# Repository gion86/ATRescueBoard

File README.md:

# ATRescueBoard
### Full credit for the original version to Jeff Keyzer [http://mightyohm.com](http://mightyohm.com)

Atmel "rescue" board for ATMega and ATTiny X4/X5: to recover fuses setting with High Voltage Programming. 

The PCB is a simplified Arduino shield, with sockets for ATMega and ATTiny; as 12V source the Vin Arduino 
pin has to be used, so the **Arduino must be powered externally with a 12V power supply!**

The micro code is uploaded to the ATmega328P on the Arduino, and comunicate with the user via the serial
interface. Three different mode can be selected:
* ATMEGA: mode for ATmega 128/168/328;
* TINY2313: not supported in this hardware version, look for original version at [https://mightyohm.com/blog/products/hv-rescue-shield-2-x/](https://mightyohm.com/blog/products/hv-rescue-shield-2-x/);
* HVSP: mode for ATtiny X4/X5;

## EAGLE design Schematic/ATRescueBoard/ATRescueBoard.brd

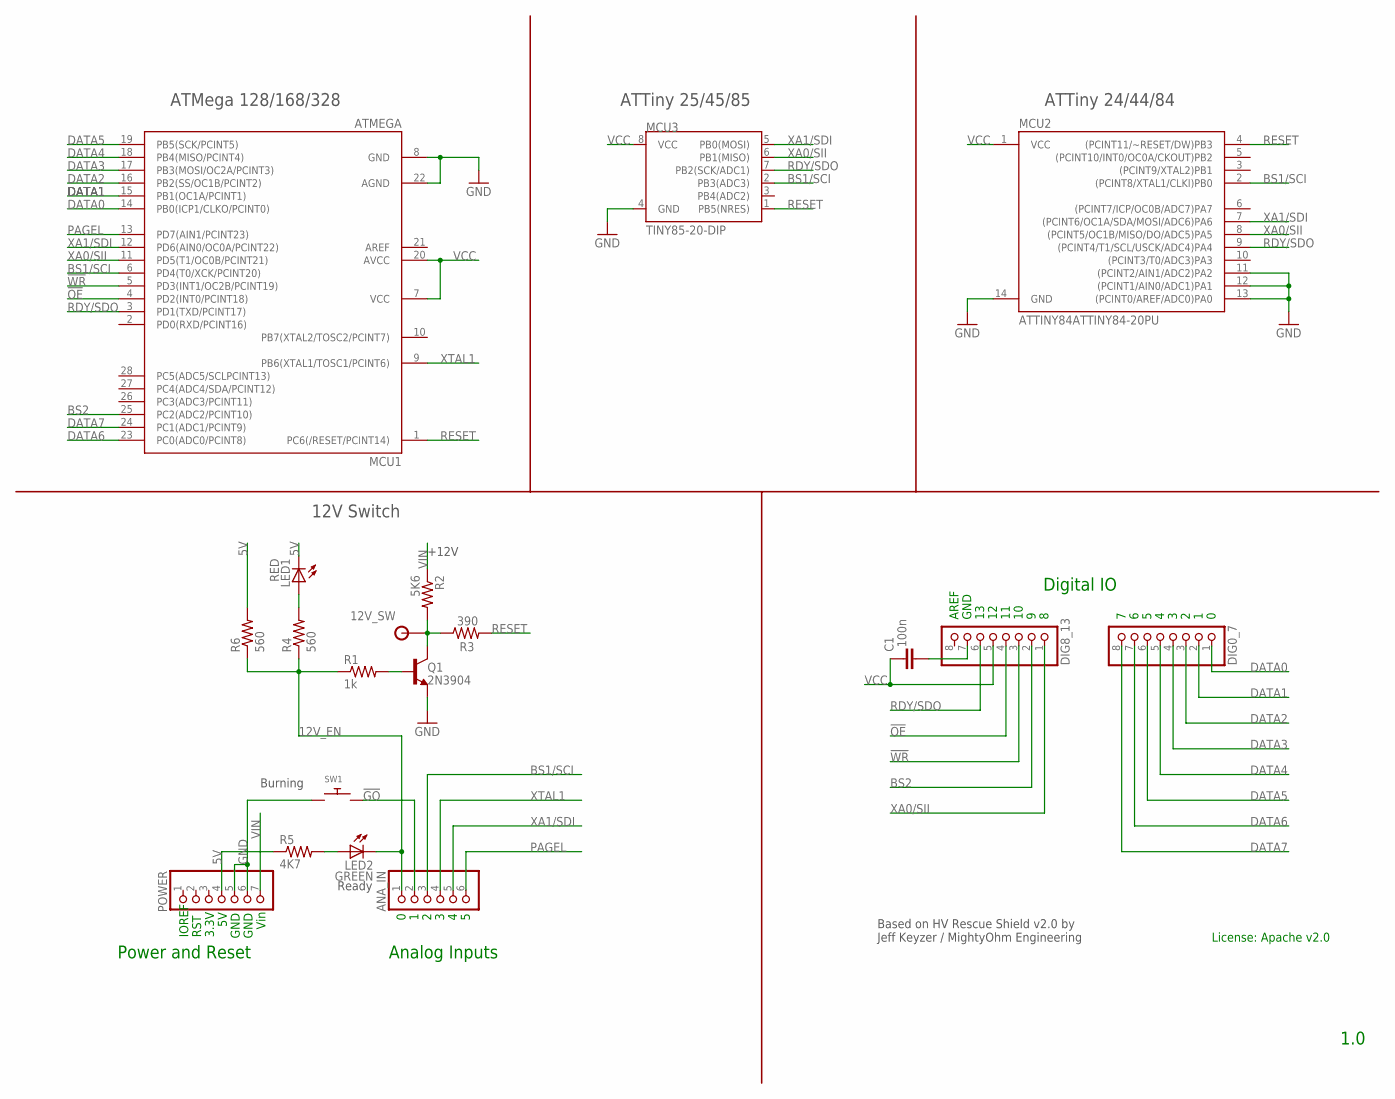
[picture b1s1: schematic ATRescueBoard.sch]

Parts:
ANA_IN: PINHD-1X6; 1X06
C1: 100n; C050-024X044
DIG0_7, DIG8_13: PINHD-1X8; 1X08
LED1: RED; LED5MM
LED2: GREEN; LED5MM
MCU1: ATMEGA; DIL28-3
MCU2: ATTINY84ATTINY84-20PU; DIL14
MCU3: TINY85-20-DIP; DIP08
POWER: PINHD-1X7; 1X07
Q1: 2N3904; TO92-
R1: 1k; 0204/7
R2: 5K6; 0207/10
R3: 390; 0309/12
R4, R6: 560; 0309/12
R5: 4K7; 0204/7
SW1: SWITCH_PUSHBUTTONEVQ-PE; TACT_PANA-EVQ
TP1: 12V_SW; TP_PTH

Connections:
5V: LED1.K (C), POWER.4, R5.1, R6.2
12V_EN: ANA_IN.1, LED2.K (C), R1.1, R4.1, R6.1
12V_SW: Q1.1 (C), R2.2, R3.1, TP1.P$1
!GO: ANA_IN.2, SW1.P$2
!OE: DIG8_13.4, MCU1.4 (PD2(INT0/PCINT18))
!WR: DIG8_13.3, MCU1.5 (PD3(INT1/OC2B/PCINT19))
BS1/SCI: ANA_IN.3, MCU1.6 (PD4(T0/XCK/PCINT20)), MCU2.2 ((PCINT8/XTAL1/CLKI)PB0), MCU3.2 (PB3(ADC3))
BS2: DIG8_13.2, MCU1.25 (PC2(ADC2/PCINT10))
DATA0: DIG0_7.1, MCU1.14 (PB0(ICP1/CLKO/PCINT0))
DATA1: DIG0_7.2, MCU1.15 (PB1(OC1A/PCINT1))
DATA2: DIG0_7.3, MCU1.16 (PB2(SS/OC1B/PCINT2))
DATA3: DIG0_7.4, MCU1.17 (PB3(MOSI/OC2A/PCINT3))
DATA4: DIG0_7.5, MCU1.18 (PB4(MISO/PCINT4))
DATA5: DIG0_7.6, MCU1.19 (PB5(SCK/PCINT5))
DATA6: DIG0_7.7, MCU1.23 (PC0(ADC0/PCINT8))
DATA7: DIG0_7.8, MCU1.24 (PC1(ADC1/PCINT9))
GND: MCU1.8 (GND), MCU1.22 (AGND), MCU2.11 ((PCINT2/AIN1/ADC2)PA2), MCU2.12 ((PCINT1/AIN0/ADC1)PA1), MCU2.13 ((PCINT0/AREF/ADC0)PA0), MCU2.14 (GND), MCU3.4 (GND), POWER.5, POWER.6, Q1.3 (E), SW1.P$1
unnamed: Q1.2 (B), R1.2
unnamed: LED1.A, R4.2
unnamed: LED2.A, R5.2
unnamed: C1.1, DIG8_13.7
PAGEL: ANA_IN.6, MCU1.13 (PD7(AIN1/PCINT23))
RDY/SDO: DIG8_13.6, MCU1.3 (PD1(TXD/PCINT17)), MCU2.9 ((PCINT4/T1/SCL/USCK/ADC4)PA4), MCU3.7 (PB2(SCK/ADC1))
RESET: MCU1.1 (PC6(/RESET/PCINT14)), MCU2.4 ((PCINT11/~RESET/DW)PB3), MCU3.1 (PB5(NRES)), R3.2
VCC: C1.2, DIG8_13.5, MCU1.7 (VCC), MCU1.20 (AVCC), MCU2.1 (VCC), MCU3.8 (VCC)
VIN: POWER.7, R2.1
XA0/SII: DIG8_13.1, MCU1.11 (PD5(T1/OC0B/PCINT21)), MCU2.8 ((PCINT5/OC1B/MISO/DO/ADC5)PA5), MCU3.6 (PB1(MISO))
XA1/SDI: ANA_IN.5, MCU1.12 (PD6(AIN0/OC0A/PCINT22)), MCU2.7 ((PCINT6/OC1A/SDA/MOSI/ADC6)PA6), MCU3.5 (PB0(MOSI))
XTAL1: ANA_IN.4, MCU1.9 (PB6(XTAL1/TOSC1/PCINT6))

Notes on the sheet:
Analog Inputs
Power and Reset
Digital IO
Vin
GND
RST
3.3V
Based on HV Rescue Shield v2.0 by Jeff Keyzer / MightyOhm Engineering
AREF
Ready
Burning
License: Apache v2.0
IOREF
+12V
ATTiny 25/45/85
ATMega 128/168/328
ATTiny 24/44/84
12V Switch

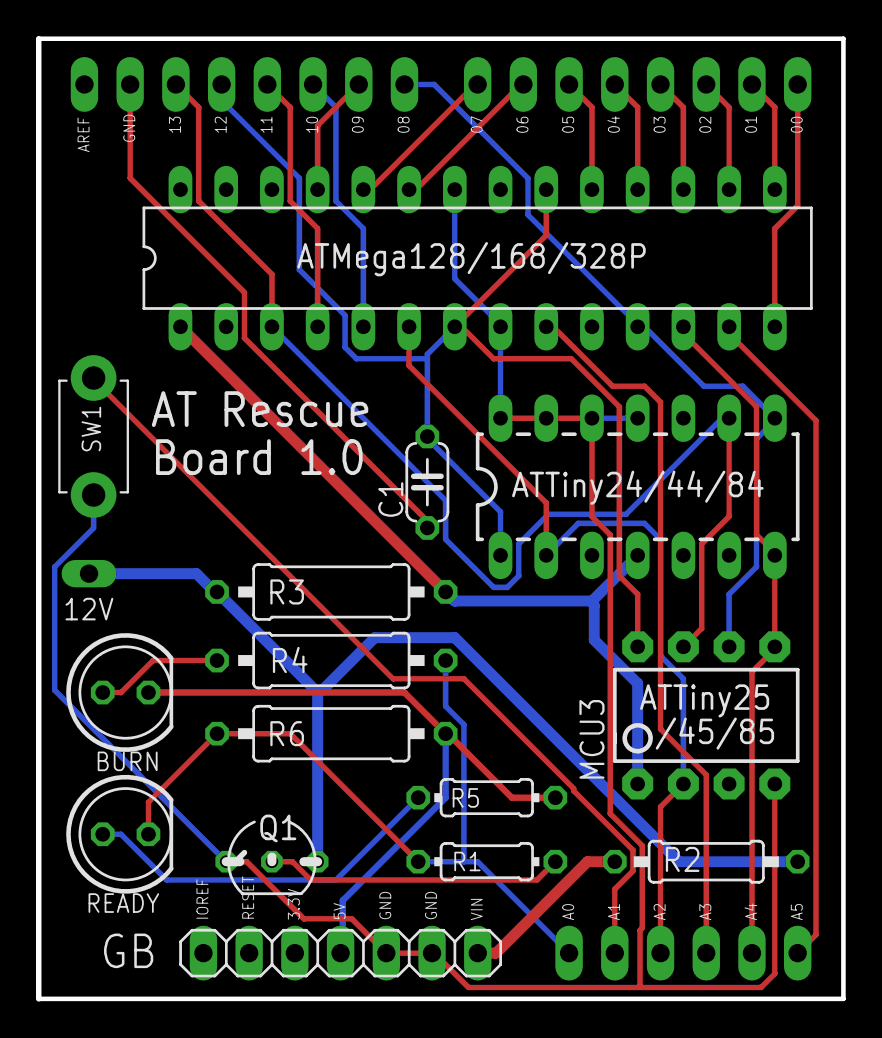
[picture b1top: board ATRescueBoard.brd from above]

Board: 2 copper layers, 44.7 x 53.3 mm, 20 parts (0 on the bottom side), 29 nets.

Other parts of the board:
DRILEGEND: DRILEGEND

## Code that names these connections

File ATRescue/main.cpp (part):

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    - modified non-interactive mode so that read/verify serial comms still occur, but fuse values aren't prompted

  12/17/10 2.01
    - added missing braces to if(mode == HVSP) that sets SDO pinmode to INPUT
    - removed misleading comment about removing AVR when entering fuse values
    - default mode changed back to ATMEGA

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#define  XA0     8
#define  XA1     A4
#define  RST     A0     // 12V Step up converter enable (12V_EN)
#define  XTAL1   A3
#define  BUTTON  A1     // Run button

// Pin assignments for HVSP mode
#define  SCI    BS1
#define  SDO    RDY
#define  SII    XA0
#define  SDI    XA1

// Serial instructions for HVSP mode
// Based on the ATtiny85 datasheet Table 20-16 pg. 163-165.
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// These pin assignments change depending on which chip is being programmed,
// so they can't be set using #define
// There is probably a more elegant way to do this.  Suggestions?
byte PAGEL = A5;  // ATtiny2313: PAGEL = BS1
byte BS2 = 9;     // ATtiny2313: BS2 = XA1


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  // I do this by shifting the byte left 1 bit at a time and checking the value of the new MSB
  for (int i=0; i<8; i++) {  // i is bit number
    if ((data << i) & 0x80)  // shift data byte left and check if new MSB is 1 or 0
      digitalWrite(SDI, HIGH);  // bit was 1, set pin high
    else
      digitalWrite(SDI, LOW);   // bit was 0, set pin low

    if ((instr << i) & 0x80)   // same process for instruction byte
      digitalWrite(SII, HIGH);
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  // I do this by shifting the byte left 1 bit at a time and checking the value of the new MSB
  for (int i=0; i<8; i++) {  // i is bit number
    if ((data << i) & 0x80)  // shift data byte left and check if new MSB is 1 or 0
      digitalWrite(SDI, HIGH);  // bit was 1, set pin high
    else
      digitalWrite(SDI, LOW);   // bit was 0, set pin low

    if ((instr << i) & 0x80)  // same process for instruction byte
      digitalWrite(SII, HIGH);
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  pinMode(BS1, OUTPUT);
  pinMode(XA0, OUTPUT);
  pinMode(XA1, OUTPUT);
  pinMode(PAGEL, OUTPUT);
  pinMode(RST, OUTPUT);  // enable signal for DC-DC converter that generates +12V !RESET
  pinMode(BS2, OUTPUT);
  pinMode(XTAL1, OUTPUT);

  pinMode(BUTTON, INPUT);
  digitalWrite(BUTTON, HIGH);  // turn on internal pullup resistor
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  digitalWrite(OE, LOW);

  if(mode == HVSP) {
    digitalWrite(SDI, LOW);  // set necessary pin values to enter programming mode
    digitalWrite(SII, LOW);
    pinMode(SDO, OUTPUT);    // SDO is same as RDY pin
    digitalWrite(SDO, LOW);  // needs to be low to enter programming mode
  }

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  if(mode == HVSP) {
    // reset SDO after short delay, longer leads to logic contention because target sets SDO high after entering programming mode
    delayMicroseconds(1);   // datasheet says 10us, 1us is needed to avoid drive contention on SDO
    pinMode(SDO, INPUT);    // set to input to avoid logic contention
  }

  delayMicroseconds(10);  // Give lots of time for part to enter programming mode
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
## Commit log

2018-04-04 Added first version of schematic and board. Arduino Uno code tested on breadboard
2018-04-15 Completed first version of schematic and board
2018-04-15 removed ignored files
2018-04-22 Added ground plane on brd and printed brd and sch pdf
2018-05-17 Added fist version of gerber file for SeeedStudio
2018-06-05 Made gerber file for board v1.0, ready for SeeedStudio
2018-06-08 Reviewed tNames layer for labels in board file
2018-06-12 Rerun cam on brd file to upload to SeeedStudio, deleted PNG folder

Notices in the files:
ATRescue/main.cpp:
Copyright 2008, 2009, 2010 Jeff Keyzer
This program is free software: you can redistribute it and/or modify
it under the terms of the GNU General Public License as published by
the Free Software Foundation, either version 3 of the License, or
(at your option) any later version.
parts and their libraries:
SparkFun-DigitalIC: Licensing: Creative Commons ShareAlike 4.0 International - https://creativecommons.org/licenses/by-sa/4.0
